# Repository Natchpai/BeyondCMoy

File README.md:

# BeyondCMoy

**Headphone Amplifier**

> Upgrade NORMAL Headphone Amplifier that my old classwork to something new.

## ✨ Features
- **Inputs:** Bluetooth and 3.5mm Aux jack
- **Battery:** Lithium polymer
- **Charging:** Via USB-C

## 📄 License

This project is licensed under the MIT License. See the [LICENSE](LICENSE) file for details.

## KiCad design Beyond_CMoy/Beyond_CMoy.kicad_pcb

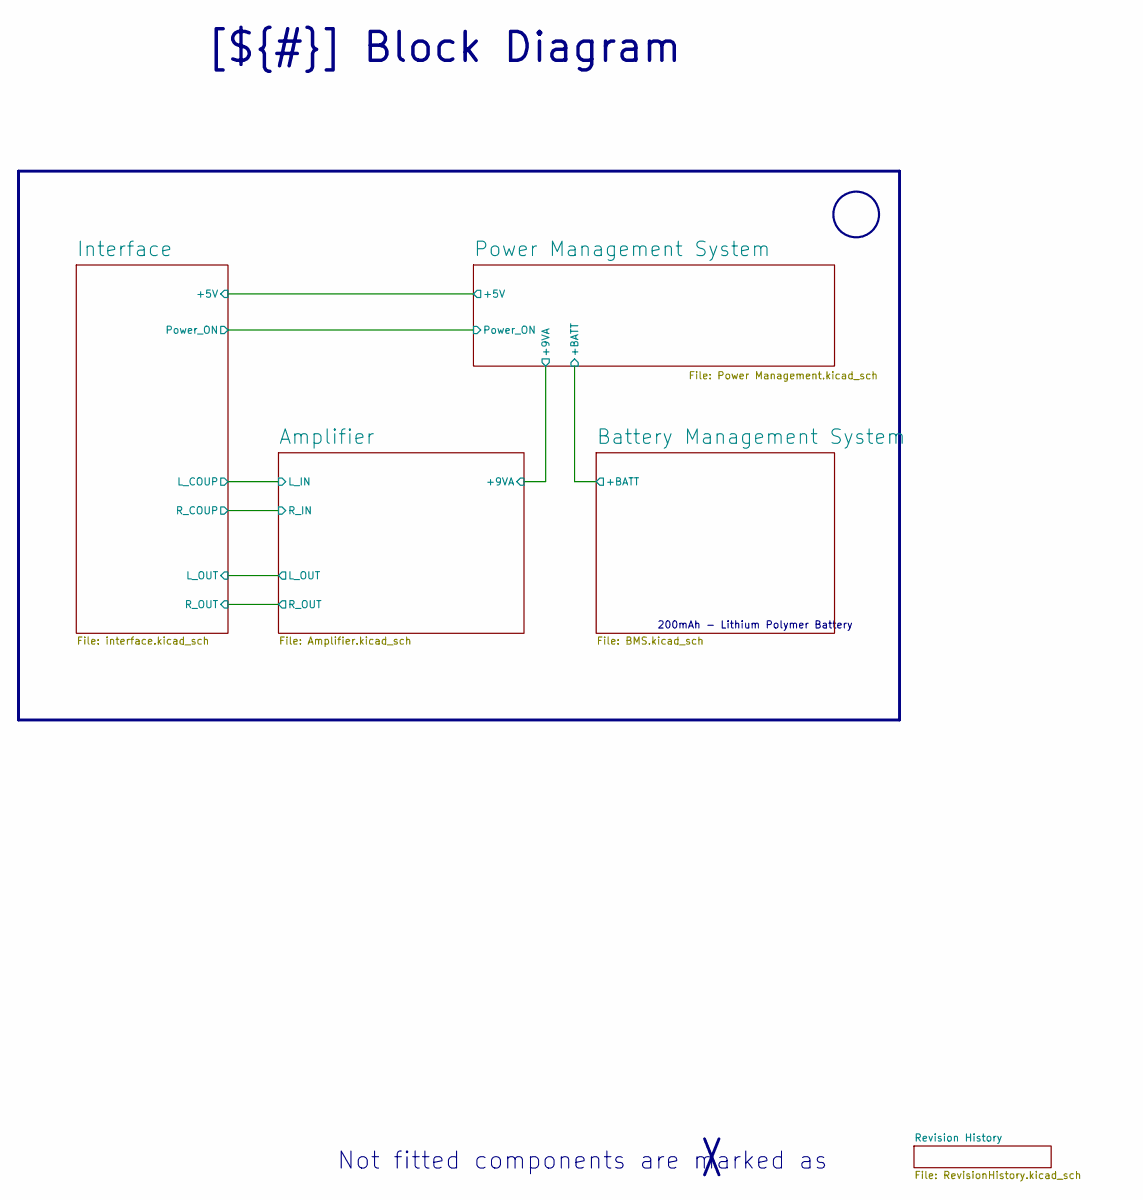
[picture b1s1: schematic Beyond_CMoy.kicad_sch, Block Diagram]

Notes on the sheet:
[${#}] ${TITLE}
200mAh - Lithium Polymer Battery
Not fitted components are marked as

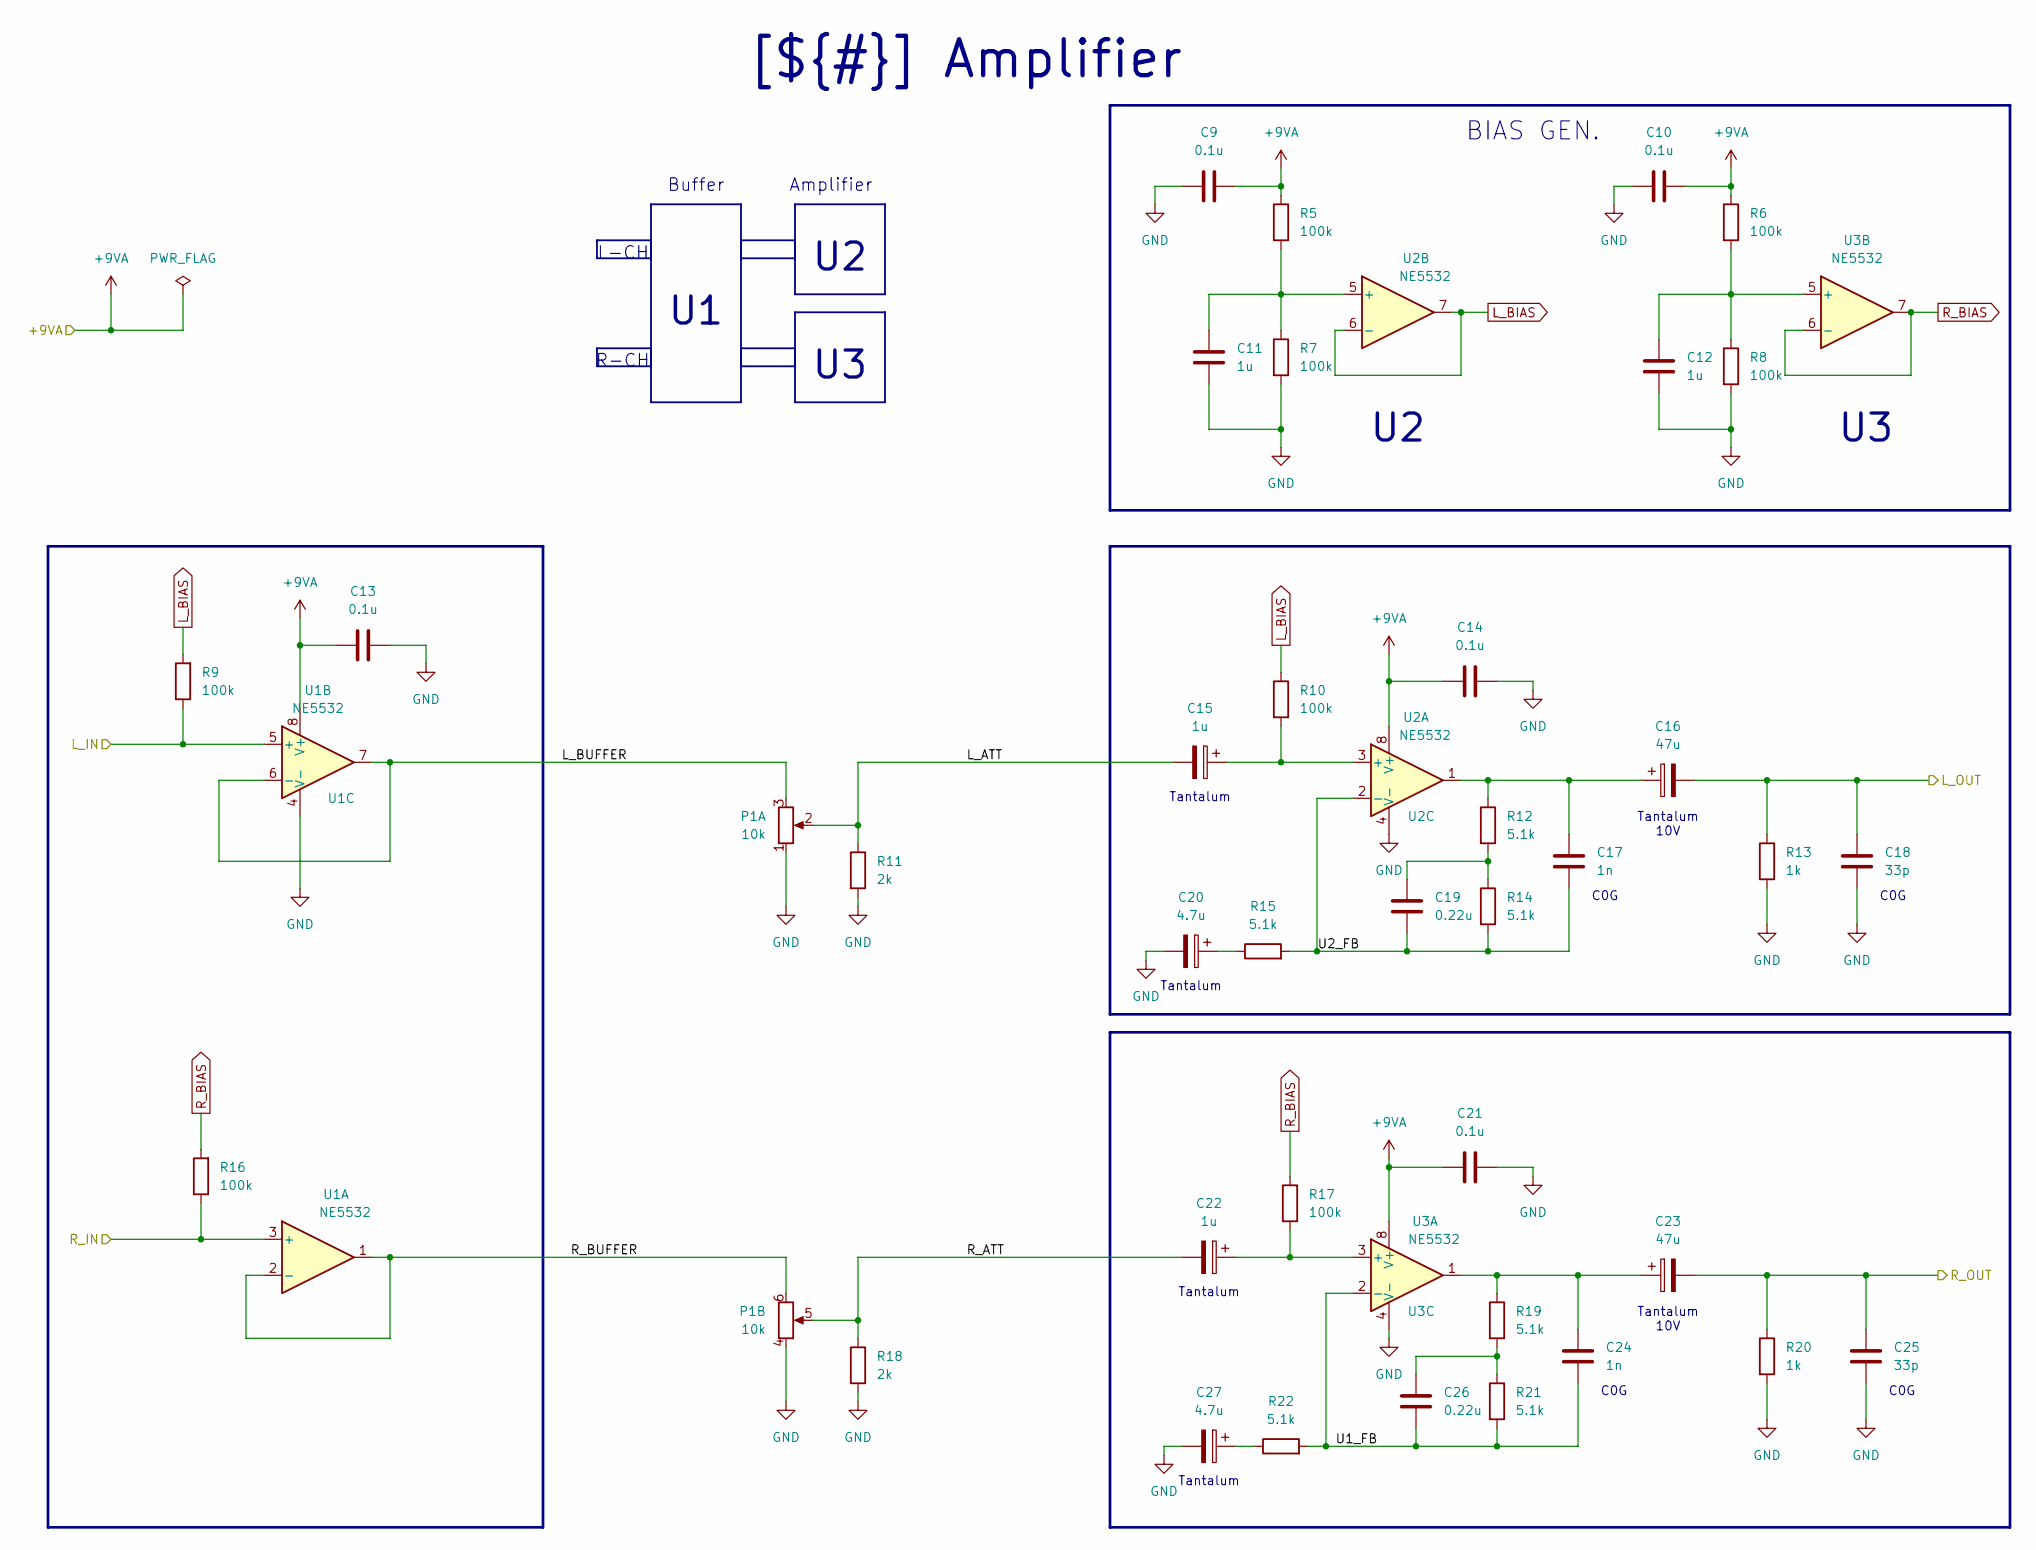
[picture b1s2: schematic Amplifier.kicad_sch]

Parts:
C9, C10, C13, C14, C21: 0.1u; C_0402_1005Metric; Mf. Part Number GRM155R71H104KE14D
C11, C12: 1u; 0_C_0805_Edited; Mf. Part Number CL21B105KBFNNNE
C15, C22: 1u; CP_EIA-3216-18_Kemet-A; Mf. Part Number TAJA105M016RNJ
C16, C23: 47u; CP_EIA-3528-21_Kemet-B; Mf. Part Number TAJB476K010RNJ
C17, C24: 1n; C_0603_1608Metric; Mf. Part Number GRM1885C2A102JA01J
C18, C25: 33p; C_0402_1005Metric; Mf. Part Number 04025A330JAT2A
C19, C26: 0.22u; C_0603_1608Metric; Mf. Part Number GRM188R71E224KA88D
C20, C27: 4.7u; CP_EIA-3528-21_Kemet-B; Mf. Part Number TAJB475K016RNJ
P1: 10k; 0_RK097GS_Dual_Horizontal_Switch; Mf. Part Number RK097GS
R5, R6, R7, R8, R9, R10, R16, R17: 100k; R_0603_1608Metric; Mf. Part Number 0603WAF1003T5E
R11, R18: 2k; R_0603_1608Metric; Mf. Part Number 0603WAF2001T5E
R12, R14, R19, R21: 5.1k; R_0603_1608Metric; Mf. Part Number 0603WAF5101T5E
R13, R20: 1k; R_0603_1608Metric; Mf. Part Number MCR03ERTF1001
R15, R22: 5.1k; R_0603_1608Metric; Mf. Part Number 0603WAF2001T5E
U1, U2, U3: NE5532; SOIC-8_3.9x4.9mm_P1.27mm; Mf. Part Number NE5532

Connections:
+9VA: C9.2, C10.2, C13.1, C14.1, C21.1, R5.1, R6.1, U1.8 (V+), U2.8 (V+), U3.8 (V+); also elsewhere on the board
/Amplifier/L_ATT: C15.2, P1.2, R11.1
/Amplifier/L_BUFFER: P1.3, U1.6 (-), U1.7
/Amplifier/R_ATT: C22.2, P1.5, R18.1
/Amplifier/R_BUFFER: P1.6, U1.1, U1.2 (-)
/Amplifier/U1_FB: C24.2, C26.2, R21.2, R22.2, U3.2 (-)
/Amplifier/U2_FB: C17.2, C19.2, R14.2, R15.2, U2.2 (-)
/Interface/L_COUP: R9.1, U1.5 (+); also elsewhere on the board
/Interface/L_OUT: C16.2, C18.1, R13.1; also elsewhere on the board
/Interface/R_COUP: R16.1, U1.3 (+); also elsewhere on the board
/Interface/R_OUT: C23.2, C25.1, R20.1; also elsewhere on the board
GND: C9.1, C10.1, C11.2, C12.2, C13.2, C14.2, C18.2, C20.2, C21.2, C25.2, C27.2, P1.1, P1.4, R7.2, R8.2, R11.2, R13.2, R18.2, R20.2, U1.4 (V-), U2.4 (V-), U3.4 (V-); also elsewhere on the board
L_BIAS: R9.2, R10.1, U2.6 (-), U2.7
unnamed: C16.1, C17.1, R12.1, U2.1
unnamed: C19.1, R12.2, R14.1
unnamed: C20.1, R15.1
unnamed: C23.1, C24.1, R19.1, U3.1
unnamed: C26.1, R19.2, R21.1
unnamed: C27.1, R22.1
unnamed: C15.1, R10.2, U2.3 (+)
unnamed: C11.1, R5.2, R7.1, U2.5 (+)
unnamed: C22.1, R17.2, U3.3 (+)
unnamed: C12.1, R6.2, R8.1, U3.5 (+)
R_BIAS: R16.2, R17.1, U3.6 (-), U3.7

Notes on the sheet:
Tantalum
L-CH
C0G
Buffer
Tantalum 10V
R-CH
[${#}] ${TITLE}
Amplifier
BIAS GEN.

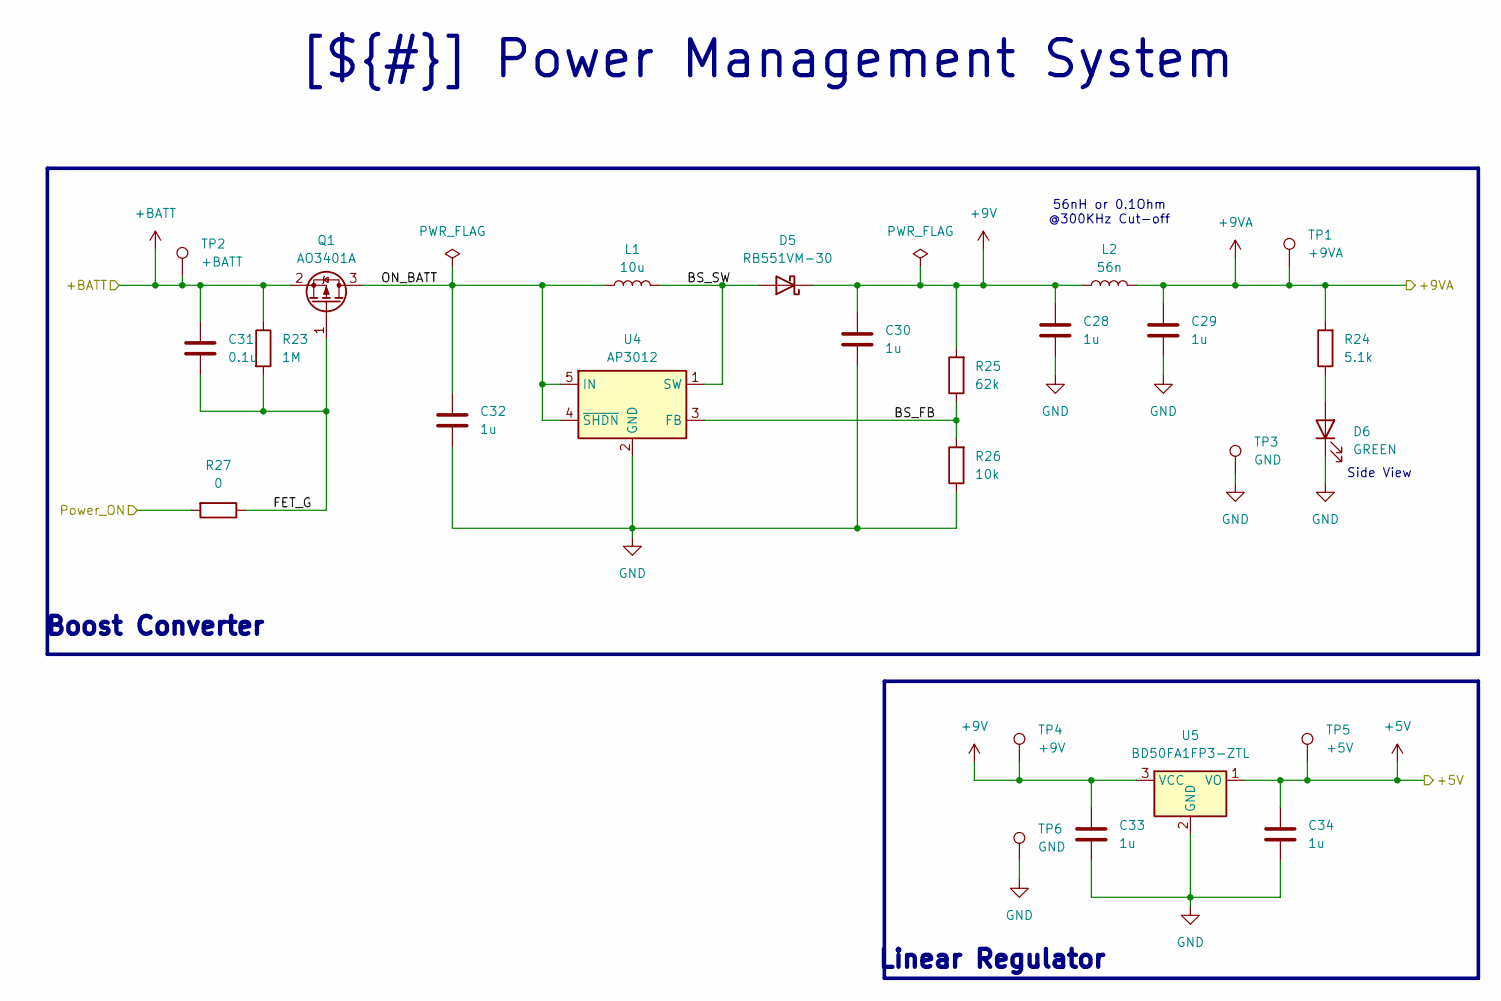
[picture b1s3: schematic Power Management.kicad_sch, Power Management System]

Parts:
C28, C29, C30, C32, C33, C34: 1u; 0_C_0805_Edited; Mf. Part Number CL21B105KBFNNNE
C31: 0.1u; C_0402_1005Metric; Mf. Part Number GRM155R71H104KE14D
D5: RB551VM-30; D_SOD-323F; Mf. Part Number RB551VM-30TE-17
D6: GREEN; LED_Kingbright_APA1606_1.6x0.6mm_Horizontal; Mf. Part Number LTST-S270KGKT
L1: 10u; 0_L_1008_Edited; Mf. Part Number DFE252010F-100M=P2
L2: 56n; L_0603_1608Metric; Mf. Part Number LQW18AN56NG00D
Q1: AO3401A; SOT-23-3; Mf. Part Number AO3401A
R23: 1M; R_0603_1608Metric; Mf. Part Number 0603WAF0000T5E
R24: 5.1k; R_0603_1608Metric; Mf. Part Number 0603WAF5101T5E
R25: 62k; R_0603_1608Metric; Mf. Part Number 0603WAF6202T5E
R26: 10k; R_0603_1608Metric; Mf. Part Number 0603WAF1002T5E
R27: 0; R_0603_1608Metric; Mf. Part Number 0603WAF5101T5E
TP1: +9VA; TestPoint_Pad_D2.0mm
TP2: +BATT; TestPoint_Pad_D2.0mm
TP3, TP6: GND; TestPoint_THTPad_1.5x1.5mm_Drill0.7mm
TP4: +9V; TestPoint_Pad_D2.0mm
TP5: +5V; TestPoint_Pad_D1.0mm
U4: AP3012; SOT-23-5; Mf. Part Number AP3012KTR-E1
U5: BD50FA1FP3-ZTL; SOT-89-3

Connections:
+5V: C34.1, TP5.1, U5.1 (VO); also elsewhere on the board
+9V: C28.1, C30.1, C33.1, D5.1 (K), L2.1, R25.2, TP4.1, U5.3 (VCC)
+9VA: C29.1, L2.2, R24.2, TP1.1; also elsewhere on the board
+BATT: C31.1, Q1.2 (S), R23.1, TP2.1; also elsewhere on the board
/Interface/Power_ON: R27.2; also elsewhere on the board
/Power Management System/BS_FB: R25.1, R26.2, U4.3 (FB)
/Power Management System/BS_SW: D5.2 (A), L1.2, U4.1 (SW)
/Power Management System/FET_G: C31.2, Q1.1 (G), R23.2, R27.1
/Power Management System/ON_BATT: C32.1, L1.1, Q1.3 (D), U4.4 (~SHDN), U4.5 (IN)
GND: C28.2, C29.2, C30.2, C32.2, C33.2, C34.2, D6.1 (K), R26.1, TP3.1, TP6.1, U4.2 (GND), U5.2 (GND); also elsewhere on the board
unnamed: D6.2 (A), R24.1

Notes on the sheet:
Boost Converter
Linear Regulator
Side View
[${#}] ${TITLE}
56nH or 0.1Ohm @300KHz Cut-off

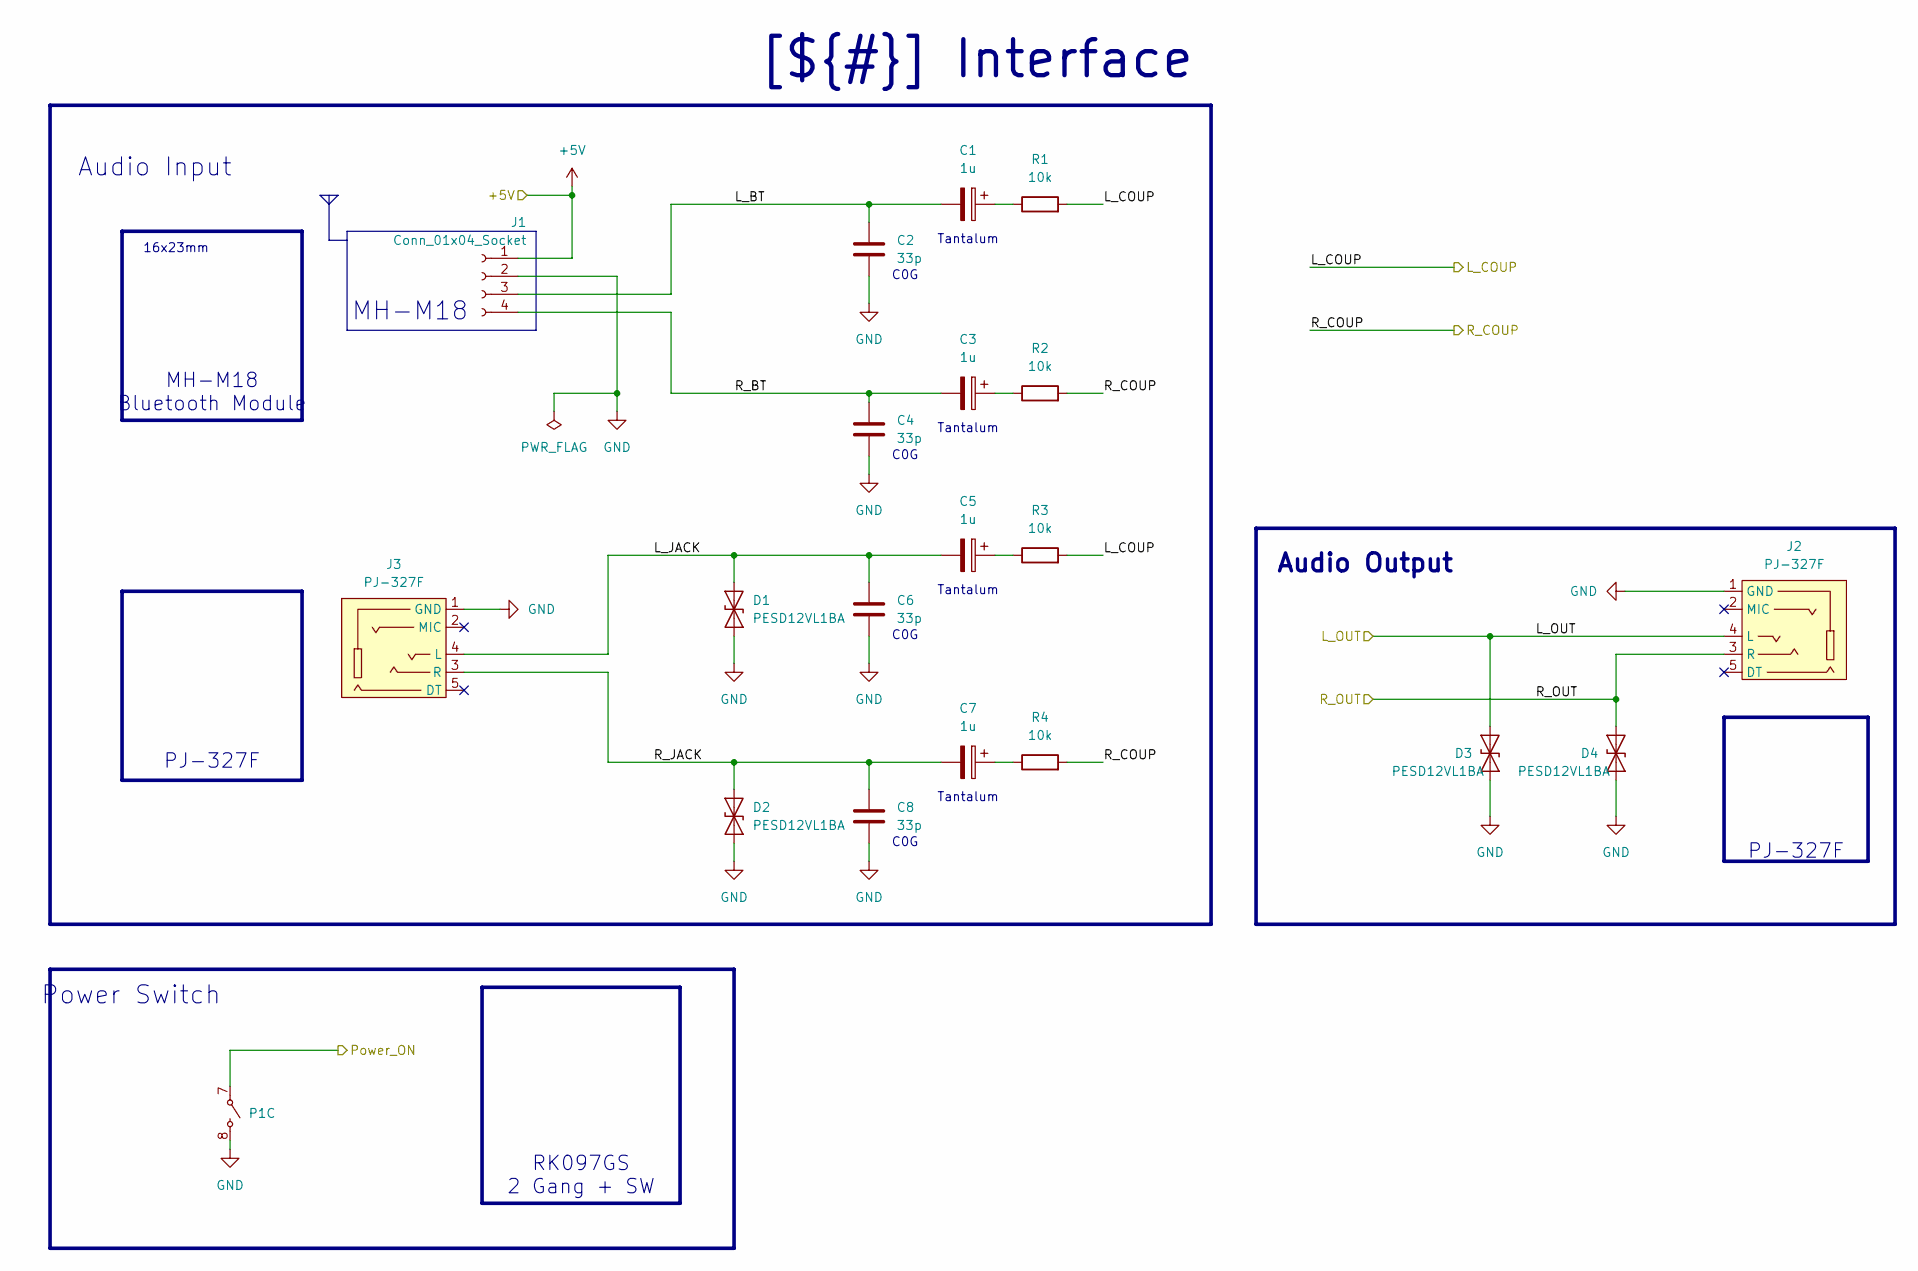
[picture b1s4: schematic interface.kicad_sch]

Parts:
C1, C3, C5, C7: 1u; CP_EIA-3216-18_Kemet-A; Mf. Part Number TAJA105M016RNJ
C2, C4, C6, C8: 33p; C_0402_1005Metric; Mf. Part Number 04025A330JAT2A
D1, D2, D3, D4: PESD12VL1BA; D_SOD-323; Mf. Part Number PESD12VL1BA
J1: Conn_01x04_Socket; PinSocket_1x04_P2.54mm_Vertical
J2, J3: PJ-327F; PJ-327F_SMD; Mf. Part Number PJ-327F
P1: 10k; 0_RK097GS_Dual_Horizontal_Switch; Mf. Part Number RK097GS
R1, R2, R3, R4: 10k; R_0603_1608Metric; Mf. Part Number 0603WAF1002T5E

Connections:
+5V: J1.1; also elsewhere on the board
/Interface/L_BT: C1.2, C2.1, J1.3
/Interface/L_COUP: R1.2, R3.2; also elsewhere on the board
/Interface/L_JACK: C5.2, C6.1, D1.2 (A2), J3.4 (L)
/Interface/L_OUT: D3.2 (A2), J2.4 (L); also elsewhere on the board
/Interface/Power_ON: P1.7; also elsewhere on the board
/Interface/R_BT: C3.2, C4.1, J1.4
/Interface/R_COUP: R2.2, R4.2; also elsewhere on the board
/Interface/R_JACK: C7.2, C8.1, D2.2 (A2), J3.3 (R)
/Interface/R_OUT: D4.2 (A2), J2.3 (R); also elsewhere on the board
GND: C2.2, C4.2, C6.2, C8.2, D1.1 (A1), D2.1 (A1), D3.1 (A1), D4.1 (A1), J1.2, J2.1 (GND), J3.1 (GND), P1.8; also elsewhere on the board
unnamed: C1.1, R1.1
unnamed: C3.1, R2.1
unnamed: C5.1, R3.1
unnamed: C7.1, R4.1

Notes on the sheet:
Tantalum
C0G
Audio Output
MH-M18
Power Switch
RK097GS 2 Gang + SW
MH-M18 Bluetooth Module
[${#}] ${TITLE}
PJ-327F
16x23mm
Audio Input

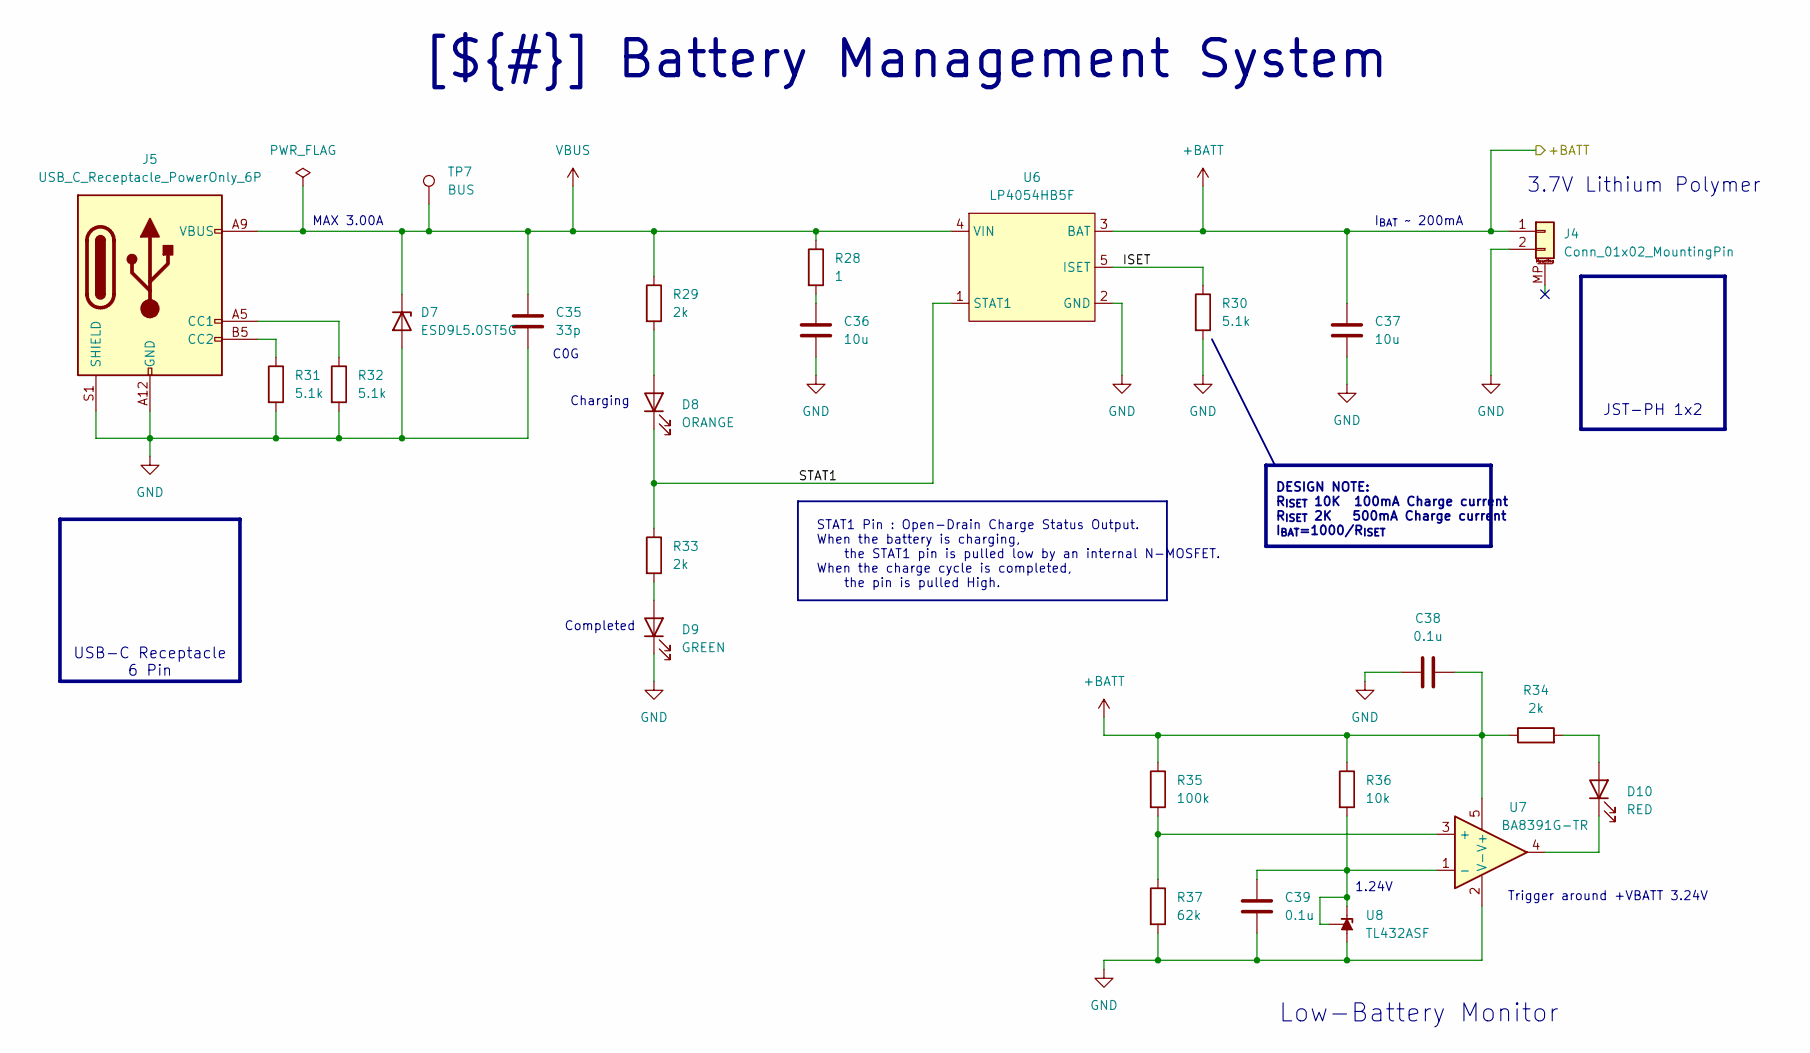
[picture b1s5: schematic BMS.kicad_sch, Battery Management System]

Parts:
C35: 33p; C_0402_1005Metric; Mf. Part Number 04025A330JAT2A
C36, C37: 10u; C_1206_3216Metric; Mf. Part Number CL31A106KBHNNNE
C38, C39: 0.1u; C_0402_1005Metric; Mf. Part Number GRM155R71H104KE14D
D7: ESD9L5.0ST5G; D_SOD-923_Edited; Mf. Part Number ESD9L5.0ST5G
D8: ORANGE; LED_0603_1608Metric; Mf. Part Number SML-D12D8WT86R
D9: GREEN; LED_0603_1608Metric; Mf. Part Number LTST-C191TGKT
D10: RED; LED_0603_1608Metric; Mf. Part Number LTST-C191KRKT
J4: Conn_01x02_MountingPin; JST_PH_S2B-PH-SM4-TB_1x02-1MP_P2.00mm_Horizontal; Mf. Part Number S2B-PH-SM4-TB
J5: USB_C_Receptacle_PowerOnly_6P; USB_C_Receptacle_GCT_USB4135-GF-A_6P_TopMnt_Horizontal; Mf. Part Number TYPEC6P019
R28: 1; R_0603_1608Metric; Mf. Part Number 0603WAF100KT5E
R29, R33, R34: 2k; R_0603_1608Metric; Mf. Part Number 0603WAF2001T5E
R30, R31, R32: 5.1k; R_0603_1608Metric; Mf. Part Number 0603WAF5101T5E
R35: 100k; R_0603_1608Metric; Mf. Part Number 0603WAF1003T5E
R36: 10k; R_0603_1608Metric; Mf. Part Number 0603WAF1002T5E
R37: 62k; R_0603_1608Metric; Mf. Part Number 0603WAF6202T5E
TP7: BUS; TestPoint_Pad_D1.0mm
U6: LP4054HB5F; SOT-23-5; Mf. Part Number LP4054H; LCSC Part C517187
U7: BA8391G-TR; SOT-23-5; Mf. Part Number BA8391G-TR
U8: TL432ASF; SOT-23; Mf. Part Number TL432ASF

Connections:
+BATT: C37.1, C38.1, J4.1, R34.1, R35.1, R36.1, U6.3 (BAT), U7.5 (V+); also elsewhere on the board
/Battery Management System/ISET: R30.1, U6.5 (ISET)
/Battery Management System/STAT1: D8.1 (K), R33.1, U6.1 (STAT1)
GND: C35.2, C36.2, C37.2, C38.2, C39.1, D7.2 (A), D9.1 (K), J4.2, J5.A12 (GND), J5.B12 (GND), J5.S1 (SHIELD), R30.2, R31.2, R32.2, R37.2, U6.2 (GND), U7.2 (V-), U8.3 (A); also elsewhere on the board
unnamed: C36.1, R28.2
unnamed: D8.2 (A), R29.2
unnamed: D9.2 (A), R33.2
unnamed: D10.2 (A), R34.2
unnamed: D10.1 (K), U7.4
unnamed: J5.A5 (CC1), R32.1
unnamed: J5.B5 (CC2), R31.1
unnamed: R35.2, R37.1, U7.3 (+)
unnamed: C39.2, R36.2, U7.1 (-), U8.1 (REF), U8.2 (K)
VBUS: C35.1, D7.1 (K), J5.A9 (VBUS), J5.B9 (VBUS), R28.1, R29.1, TP7.1, U6.4 (VIN)

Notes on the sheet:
3.7V Lithium Polymer
JST-PH 1x2
STAT1 Pin : Open-Drain Charge Status Output. When the battery is charging, the STAT1 pin is pulled low by an internal N-MOSFET. When the charge cycle is completed, the pin is pulled High.
C0G
USB-C Receptacle 6 Pin
Charging
1.24V
DESIGN NOTE: R_{ISET} 10K 100mA Charge current R_{ISET} 2K 500mA Charge current I_{BAT}=1000/R_{ISET}
Trigger around +VBATT 3.24V
MAX 3.00A
Low-Battery Monitor
I_{BAT} ~ 200mA
[${#}] ${TITLE}
Completed

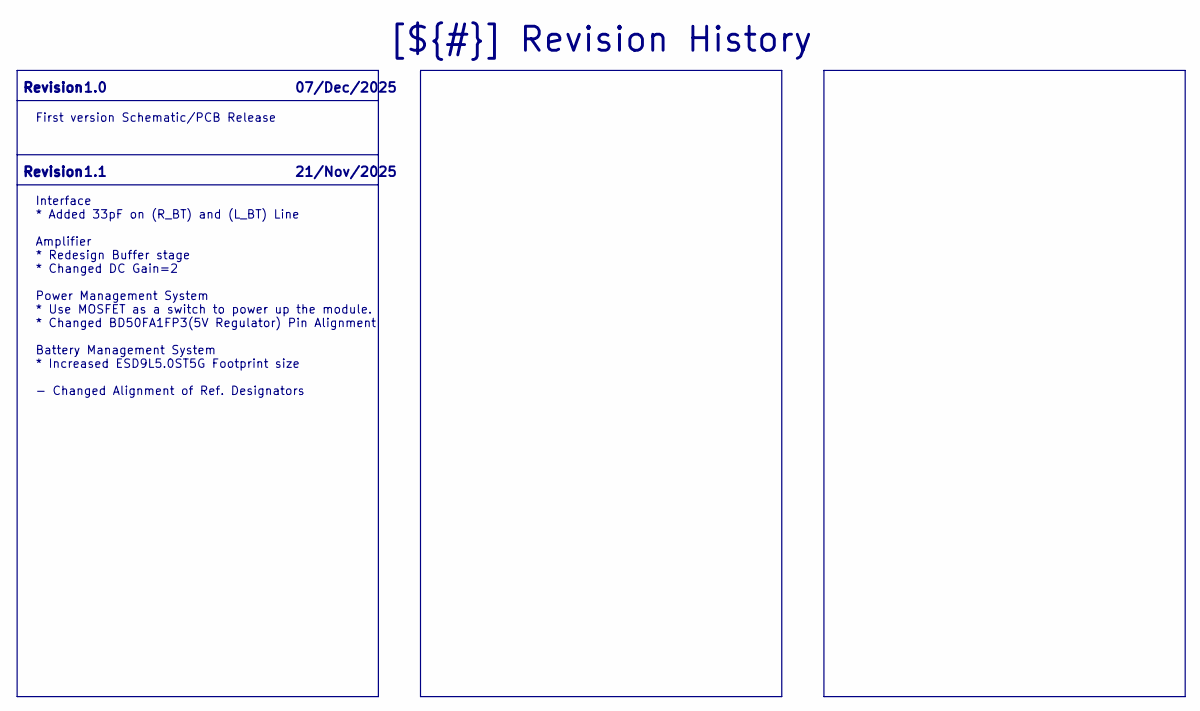
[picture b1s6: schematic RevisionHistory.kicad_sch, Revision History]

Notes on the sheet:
First version Schematic/PCB Release
Interface * Added 33pF on (R_BT) and (L_BT) Line Amplifier * Redesign Buffer stage * Changed DC Gain=2 Power Management System * Use MOSFET as a switch to power up the module. * Changed BD50FA1FP3(5V Regulator) Pin Alignment Battery Management System * Increased ESD9L5.0ST5G Footprint size - Change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
21/Nov/2025
07/Dec/2025
1.0
Revision
[${#}] ${TITLE}
1.1

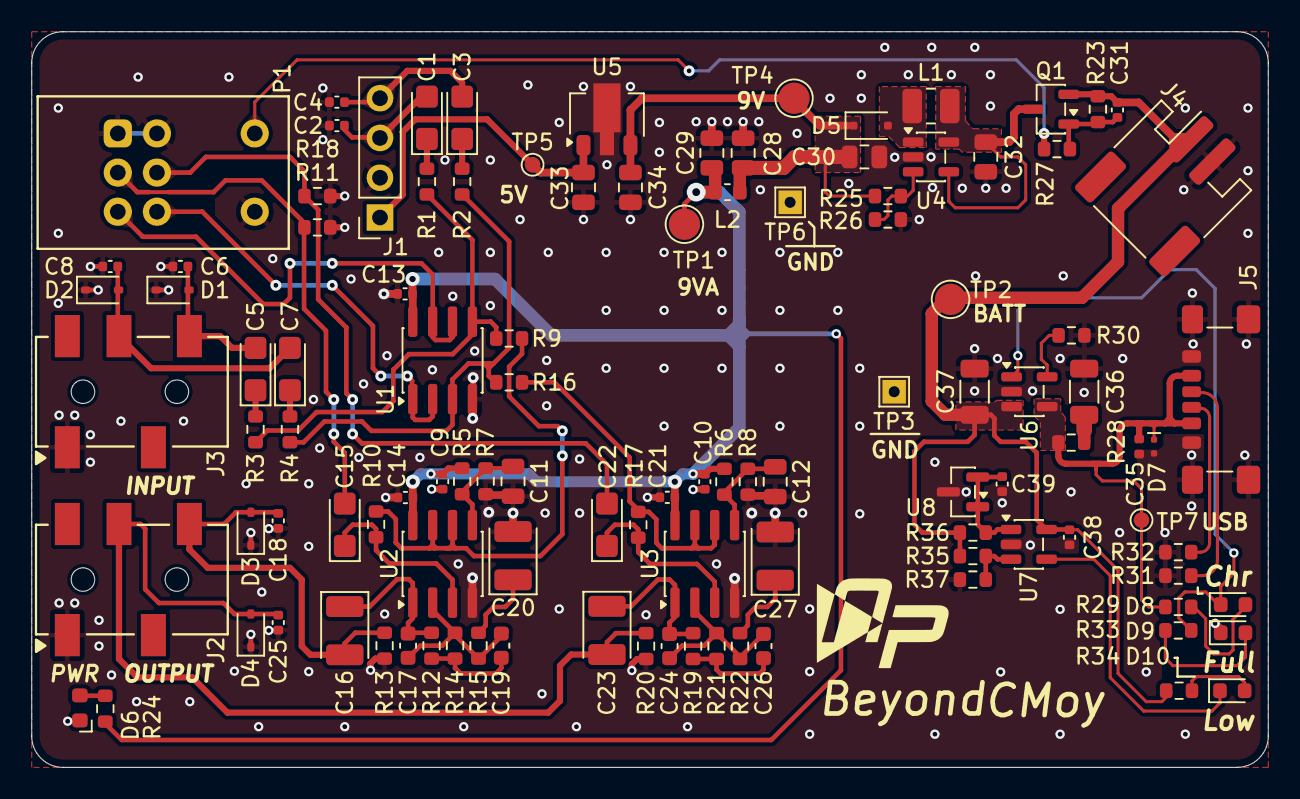
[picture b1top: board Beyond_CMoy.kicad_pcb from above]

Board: 2 copper layers, 79.0 x 47.0 mm, 111 parts (0 on the bottom side), 53 nets.

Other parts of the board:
G1: LOGO

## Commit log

2025-11-30 Added project files
2025-11-30 Create LICENSE
2025-11-30 Layout Board1
2025-11-30 KiCAD do something
2025-12-01 PCB Layout
2025-12-03 Revise description for headphone amplifier
    Updated description of the headphone amplifier.
2025-12-07 RELEASED
2025-12-08 Added 3D Render
2025-12-08 Enhance README with image and project details
    Added an image and updated project description.
2025-12-08 Modify images in README for headphone amplifier
    Updated image source in README and added a new image.
2025-12-11 Update Doc and Same verison Release
    Release v1.0 , Update Doc Files
2025-12-11 Fix image link and enhance project description
    Updated image source link in README and improved project description.
2025-12-11 Update BOM
    Edit Part Number but all the same
2025-12-18 Debugging & New Rev.
2025-12-22 Re-layout
2026-02-09 Added pdf file
